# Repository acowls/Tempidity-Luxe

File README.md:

# Tempidity-Luxe
A sensor board for TI OPT3001 Ambient Light Sensor and the TI HDC1080 Low Power, High Accuracy Digital Humidity Sensor with Temperature Sensor.

This board samples the following:
* Light (lux)
* Relative Humidity (%)
* Temperature (degrees celcius)

While this board is protyping friendly (aka bread-board) it is intdened that it be conected to a hosting board for production use. 
For accurtate readings the sensors require no objects to be near them that could reflect or generate heat. 
Having these sensors isolated on this “daughter" board provides flexibile deployment options. 
To order one go to my profile on OSH Park: [https://oshpark.com/profiles/SeaOwl]

If you are looking for libraries to use this with an Arduino then take a look here:
* https://github.com/closedcube/ClosedCube_HDC1080_Arduino
and
* https://github.com/closedcube/ClosedCube_OPT3001_Arduino
for examples.

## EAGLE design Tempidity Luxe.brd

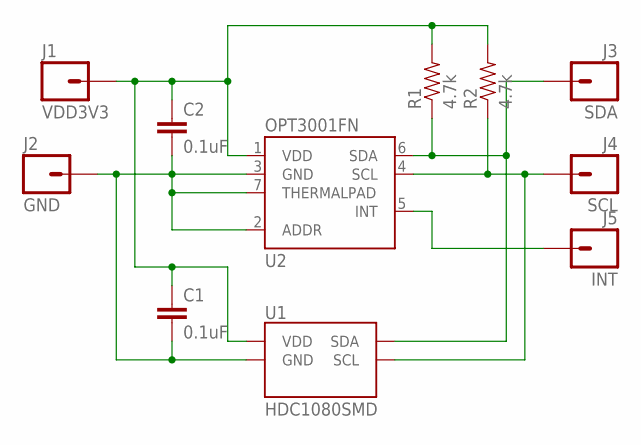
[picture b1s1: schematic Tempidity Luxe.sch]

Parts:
C1, C2: 0.1uF; 0805
J1: VDD3V3; 1X01_NO_SILK
J2: GND; 1X01_NO_SILK
J3: SDA; 1X01_NO_SILK
J4: SCL; 1X01_NO_SILK
J5: INT; 1X01_NO_SILK
R1, R2: 4.7k; 0805
U1: HDC1080SMD; TI-PWSON6-DMB
U2: OPT3001FN; TI-USON6-GND-PAD

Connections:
GND: C1.2, C2.2, J2.1, U1.GND, U2.2 (ADDR), U2.3 (GND), U2.7 (THERMALPAD)
N$INT: J5.1, U2.5 (INT)
SCL: J4.1, R2.1, U1.SCL, U2.4 (SCL)
SDA: J3.1, R1.1, U1.SDA, U2.6 (SDA)
VDD: C1.1, C2.1, J1.1, R1.2, R2.2, U1.VDD, U2.1 (VDD)

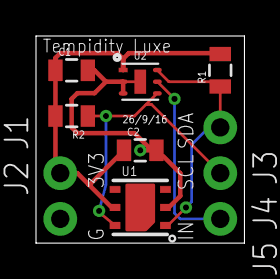
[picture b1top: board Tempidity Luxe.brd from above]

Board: 2 copper layers, 11.6 x 11.5 mm, 11 parts (0 on the bottom side), 5 nets.

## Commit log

2016-09-27 The initial build of the sensor board

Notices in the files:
parts and their libraries:
SparkFun-Capacitors: Licensing: Creative Commons ShareAlike 4.0 International - https://creativecommons.org/licenses/by-sa/4.0
